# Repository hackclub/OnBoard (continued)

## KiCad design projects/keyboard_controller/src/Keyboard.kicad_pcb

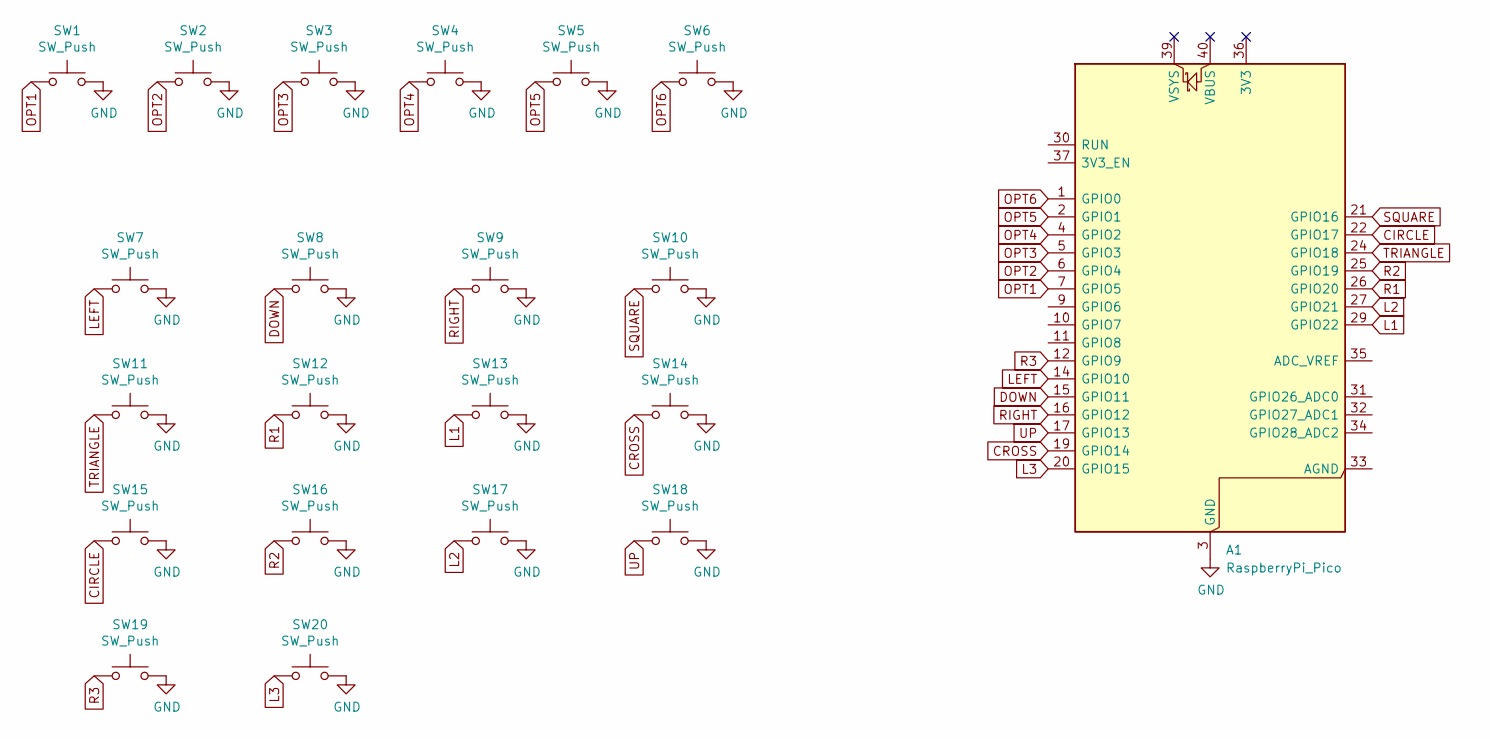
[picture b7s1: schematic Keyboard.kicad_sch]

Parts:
A1: RaspberryPi_Pico; RaspberryPi_Pico_Common_Unspecified
SW1, SW2, SW3, SW4, SW5, SW6: SW_Push; SW_PUSH_6mm_H5mm
SW7, SW8, SW9, SW10, SW11, SW12, SW13, SW14, SW15, SW16, SW17, SW18, SW19, SW20: SW_Push; Kailh_socket_PG1350_optional

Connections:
CIRCLE: A1.22 (GPIO17), SW15.1
CROSS: A1.19 (GPIO14), SW14.1
DOWN: A1.15 (GPIO11), SW8.1
GND: A1.3 (GND), A1.8 (GND), A1.13 (GND), A1.18 (GND), A1.23 (GND), A1.28 (GND), A1.38 (GND), SW1.2, SW2.2, SW3.2, SW4.2, SW5.2, SW6.2, SW7.2, SW8.2, SW9.2, SW10.2, SW11.2, SW12.2, SW13.2, SW14.2, SW15.2, SW16.2, SW17.2, SW18.2, SW19.2, SW20.2
L1: A1.29 (GPIO22), SW13.1
L2: A1.27 (GPIO21), SW17.1
L3: A1.20 (GPIO15), SW20.1
LEFT: A1.14 (GPIO10), SW7.1
OPT1: A1.7 (GPIO5), SW1.1
OPT2: A1.6 (GPIO4), SW2.1
OPT3: A1.5 (GPIO3), SW3.1
OPT4: A1.4 (GPIO2), SW4.1
OPT5: A1.2 (GPIO1), SW5.1
OPT6: A1.1 (GPIO0), SW6.1
R1: A1.26 (GPIO20), SW12.1
R2: A1.25 (GPIO19), SW16.1
R3: A1.12 (GPIO9), SW19.1
RIGHT: A1.16 (GPIO12), SW9.1
SQUARE: A1.21 (GPIO16), SW10.1
TRIANGLE: A1.24 (GPIO18), SW11.1
UP: A1.17 (GPIO13), SW18.1

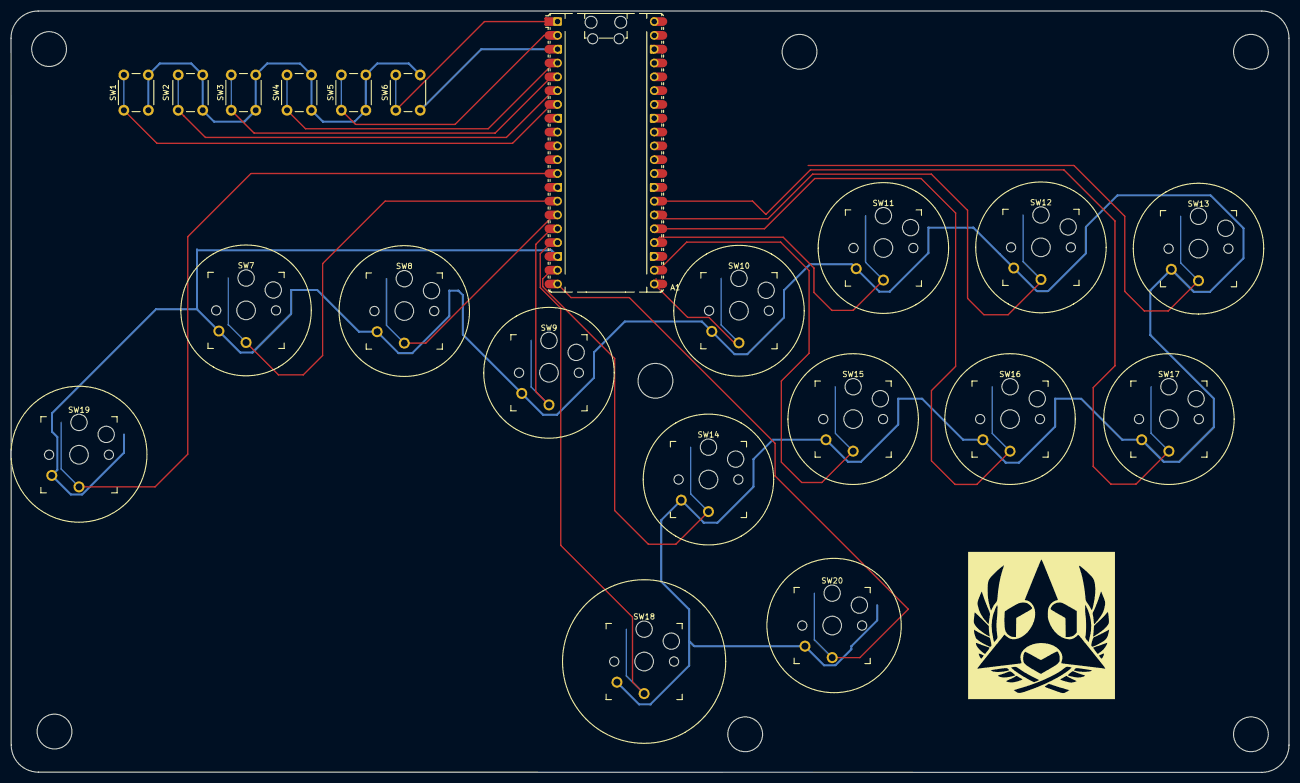
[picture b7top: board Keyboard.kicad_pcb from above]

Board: 2 copper layers, 235.0 x 140.0 mm, 21 parts (0 on the bottom side), 21 nets.
